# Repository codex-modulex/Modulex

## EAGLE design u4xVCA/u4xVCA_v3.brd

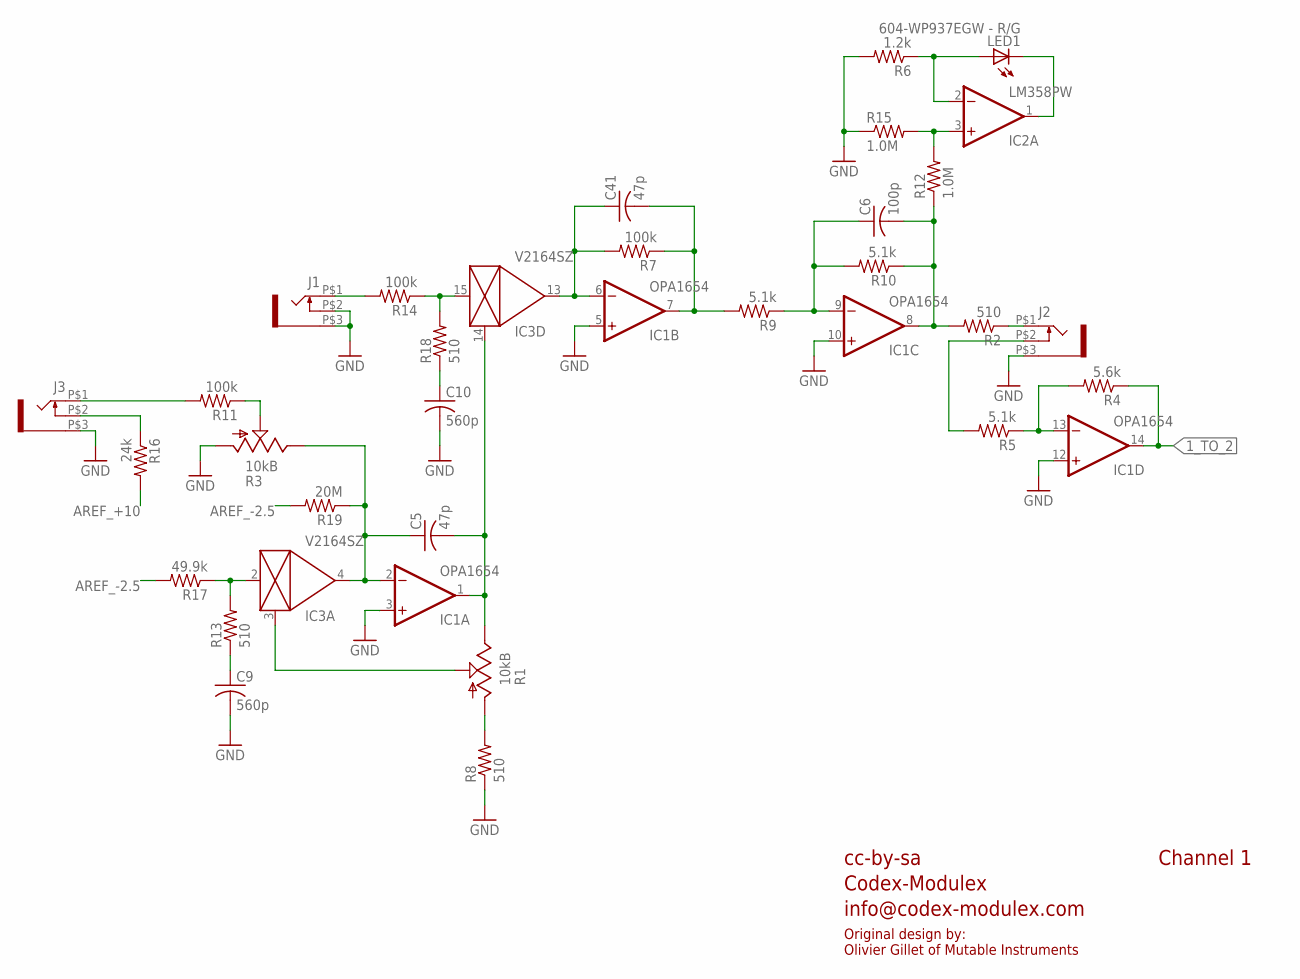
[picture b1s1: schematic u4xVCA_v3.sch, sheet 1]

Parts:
C5, C41: 47p; C0603
C6: 100p; C0603
C9, C10: 560p; C0603
IC1: OPA1654; TSSOP14
IC2: LM358PW; TSSOP8
IC3: V2164SZ; SOIC16N
J1, J2, J3: WQP-PJ301M-12_JACK
LED1: 604-WP937EGW - R/G; LED3MM
R1, R3: 10kB; ALPS_POT_VERTICAL
R2, R13, R18: 510; PARTS_AMAN_RESISTOR_0603
R4: 5.6k; PARTS_AMAN_RESISTOR_0603
R5, R9, R10: 5.1k; PARTS_AMAN_RESISTOR_0603
R6: 1.2k; PARTS_AMAN_RESISTOR_0603
R7, R11, R14: 100k; PARTS_AMAN_RESISTOR_0603
R8: 510; R0603
R12, R15: 1.0M; PARTS_AMAN_RESISTOR_0603
R16: 24k; PARTS_AMAN_RESISTOR_0603
R17: 49.9k; PARTS_AMAN_RESISTOR_0603
R19: 20M; PARTS_AMAN_RESISTOR_0603

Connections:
1_TO_2: IC1.14 (OUT), R4.1; also elsewhere on the board
AREF_+10: R16.2; also elsewhere on the board
AREF_-2.5: R17.2, R19.2; also elsewhere on the board
CV_IN_1: J3.P$1 (2), R11.2
FOO: IC3.2 (IN), R13.2, R17.1
GND: C9.2, C10.2, IC1.3 (+IN), IC1.5 (+IN), IC1.10 (+IN), IC1.12 (+IN), J1.P$2 (3), J1.P$3 (1), J2.P$3 (1), J3.P$3 (1), R3.P$3 (A), R6.2, R8.1, R15.1; also elsewhere on the board
unnamed: IC2.3 (+IN), R12.2, R15.2
unnamed: J2.P$1 (2), R2.1
unnamed: IC3.3 (CTRL), R1.P$2 (S)
unnamed: C6.1, IC1.9 (-IN), R9.1, R10.2
unnamed: R3.P$2 (S), R11.1
unnamed: R1.P$3 (A), R8.2
unnamed: IC2.1 (OUT), LED1.K (C)
unnamed: IC2.2 (-IN), LED1.A, R6.1
unnamed: C9.1, R13.1
unnamed: J3.P$2 (3), R16.1
unnamed: IC1.13 (-IN), R4.2, R5.1
unnamed: J2.P$2 (3), R5.2
unnamed: C10.1, R18.1
unnamed: C5.1, IC1.2 (-IN), IC3.4 (OUT), R3.P$1 (E), R19.1
unnamed: J1.P$1 (2), R14.2
unnamed: IC3.15 (IN), R14.1, R18.2
unnamed: C5.2, IC1.1 (OUT), IC3.14 (CTRL), R1.P$1 (E)
unnamed: C41.1, IC1.6 (-IN), IC3.13 (OUT), R7.2
unnamed: C41.2, IC1.7 (OUT), R7.1, R9.2
OUT1: C6.2, IC1.8 (OUT), R2.2, R10.1, R12.1

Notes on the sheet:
cc-by-sa
Codex-Modulex
info@codex-modulex.com
Channel 1
Original design by: Olivier Gillet of Mutable Instruments

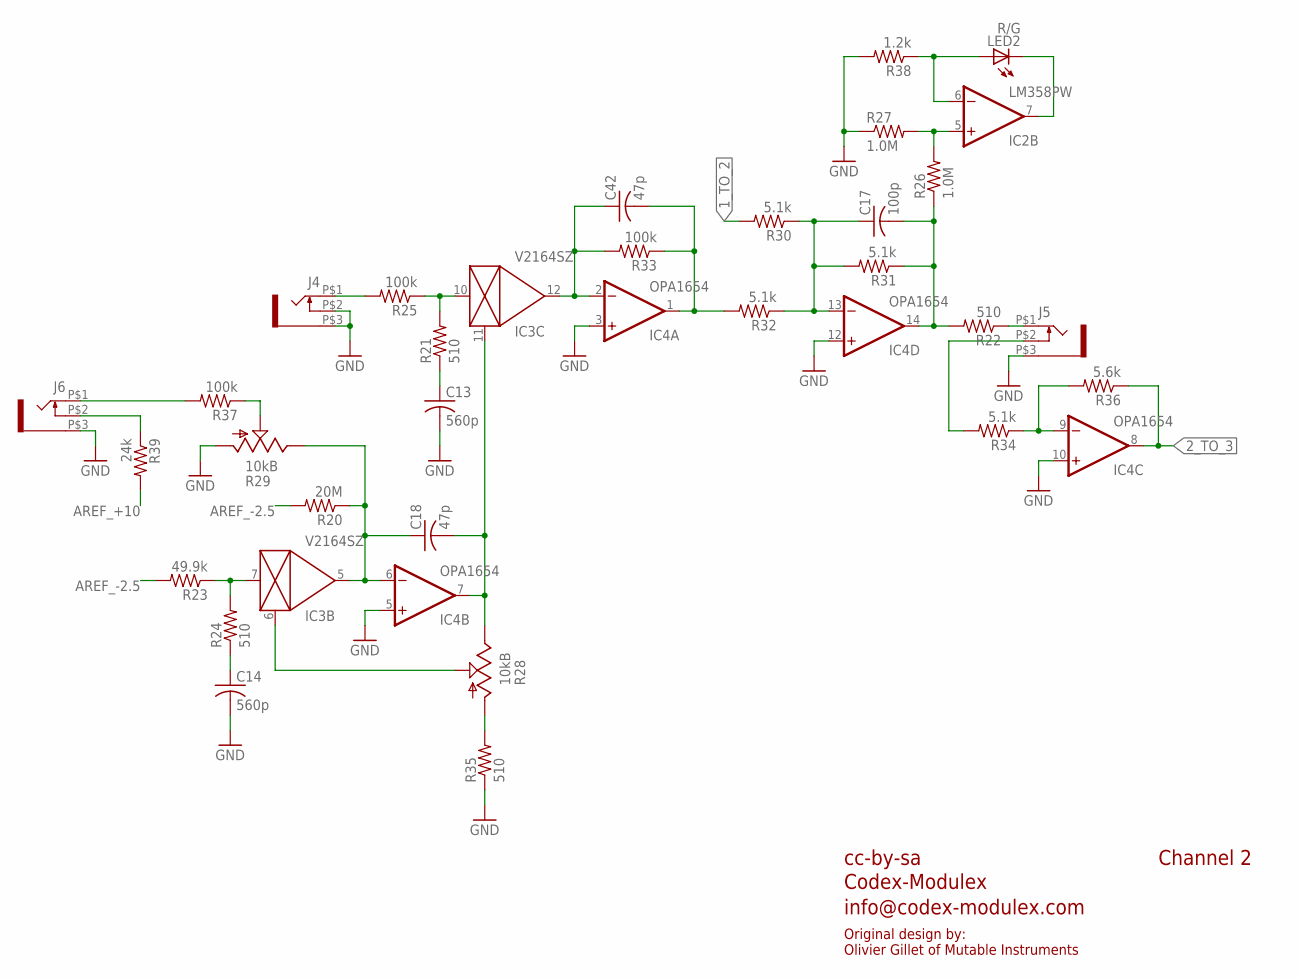
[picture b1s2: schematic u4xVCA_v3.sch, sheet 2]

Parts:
C13, C14: 560p; C0603
C17: 100p; C0603
C18, C42: 47p; C0603
IC2: LM358PW; TSSOP8
IC3: V2164SZ; SOIC16N
IC4: OPA1654; TSSOP14
J4, J5, J6: WQP-PJ301M-12_JACK
LED2: R/G; LED3MM
R20: 20M; PARTS_AMAN_RESISTOR_0603
R21, R24: 510; PARTS_AMAN_RESISTOR_0603
R22, R35: 510; R0603
R23: 49.9k; PARTS_AMAN_RESISTOR_0603
R25, R33, R37: 100k; PARTS_AMAN_RESISTOR_0603
R26, R27: 1.0M; PARTS_AMAN_RESISTOR_0603
R28, R29: 10kB; ALPS_POT_VERTICAL
R30, R31, R32, R34: 5.1k; PARTS_AMAN_RESISTOR_0603
R36: 5.6k; PARTS_AMAN_RESISTOR_0603
R38: 1.2k; PARTS_AMAN_RESISTOR_0603
R39: 24k; PARTS_AMAN_RESISTOR_0603

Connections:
1_TO_2: R30.2; also elsewhere on the board
2_TO_3: IC4.8 (OUT), R36.1; also elsewhere on the board
AREF_+10: R39.2; also elsewhere on the board
AREF_-2.5: R20.2, R23.2; also elsewhere on the board
FOO1: IC3.7 (IN), R23.1, R24.2
GND: C13.2, C14.2, IC4.3 (+IN), IC4.5 (+IN), IC4.10 (+IN), IC4.12 (+IN), J4.P$2 (3), J4.P$3 (1), J5.P$3 (1), J6.P$3 (1), R27.1, R29.P$3 (A), R35.1, R38.2; also elsewhere on the board
unnamed: J4.P$1 (2), R25.2
unnamed: IC2.5 (+IN), R26.2, R27.2
unnamed: J5.P$1 (2), R22.1
unnamed: C13.1, R21.1
unnamed: IC3.10 (IN), R21.2, R25.1
unnamed: IC3.6 (CTRL), R28.P$2 (S)
unnamed: C17.1, IC4.13 (-IN), R30.1, R31.2, R32.1
unnamed: C18.2, IC3.11 (CTRL), IC4.7 (OUT), R28.P$1 (E)
unnamed: R28.P$3 (A), R35.2
unnamed: IC2.7 (OUT), LED2.K (C)
unnamed: IC2.6 (-IN), LED2.A, R38.1
unnamed: IC4.9 (-IN), R34.1, R36.2
unnamed: J5.P$2 (3), R34.2
unnamed: C42.2, IC4.1 (OUT), R32.2, R33.1
unnamed: R29.P$2 (S), R37.1
unnamed: C14.1, R24.1
unnamed: C18.1, IC3.5 (OUT), IC4.6 (-IN), R20.1, R29.P$1 (E)
unnamed: J6.P$1 (2), R37.2
unnamed: C42.1, IC3.12 (OUT), IC4.2 (-IN), R33.2
unnamed: J6.P$2 (3), R39.1
OUT2: C17.2, IC4.14 (OUT), R22.2, R26.1, R31.1

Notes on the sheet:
cc-by-sa
Codex-Modulex
info@codex-modulex.com
Channel 2
Original design by: Olivier Gillet of Mutable Instruments

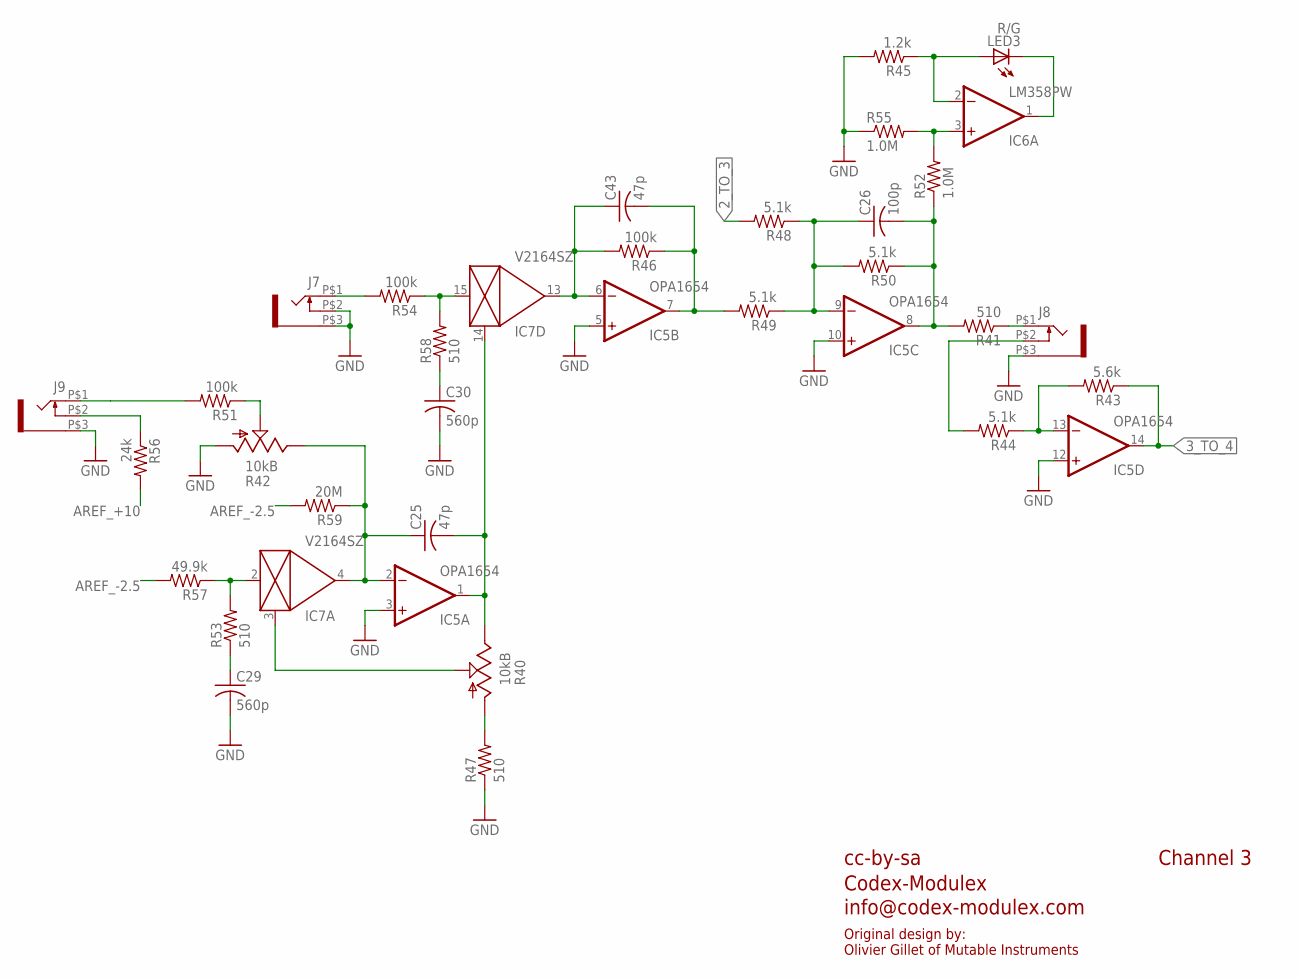
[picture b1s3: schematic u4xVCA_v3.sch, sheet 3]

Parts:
C25, C43: 47p; C0603
C26: 100p; C0603
C29, C30: 560p; C0603
IC5: OPA1654; TSSOP14
IC6: LM358PW; TSSOP8
IC7: V2164SZ; SOIC16N
J7, J8, J9: WQP-PJ301M-12_JACK
LED3: R/G; LED3MM
R40, R42: 10kB; ALPS_POT_VERTICAL
R41, R47, R53, R58: 510; PARTS_AMAN_RESISTOR_0603
R43: 5.6k; PARTS_AMAN_RESISTOR_0603
R44, R48, R49, R50: 5.1k; PARTS_AMAN_RESISTOR_0603
R45: 1.2k; PARTS_AMAN_RESISTOR_0603
R46, R51, R54: 100k; PARTS_AMAN_RESISTOR_0603
R52, R55: 1.0M; PARTS_AMAN_RESISTOR_0603
R56: 24k; PARTS_AMAN_RESISTOR_0603
R57: 49.9k; PARTS_AMAN_RESISTOR_0603
R59: 20M; PARTS_AMAN_RESISTOR_0603

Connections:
2_TO_3: R48.2; also elsewhere on the board
3_TO_4: IC5.14 (OUT), R43.1; also elsewhere on the board
AREF_+10: R56.2; also elsewhere on the board
AREF_-2.5: R57.2, R59.2; also elsewhere on the board
FOO2: IC7.2 (IN), R53.2, R57.1
GND: C29.2, C30.2, IC5.3 (+IN), IC5.5 (+IN), IC5.10 (+IN), IC5.12 (+IN), J7.P$2 (3), J7.P$3 (1), J8.P$3 (1), J9.P$3 (1), R42.P$3 (A), R45.2, R47.1, R55.1; also elsewhere on the board
unnamed: IC6.3 (+IN), R52.2, R55.2
unnamed: J8.P$1 (2), R41.1
unnamed: IC7.3 (CTRL), R40.P$2 (S)
unnamed: C25.2, IC5.1 (OUT), IC7.14 (CTRL), R40.P$1 (E)
unnamed: R40.P$3 (A), R47.2
unnamed: C30.1, R58.1
unnamed: IC7.15 (IN), R54.1, R58.2
unnamed: C26.1, IC5.9 (-IN), R48.1, R49.1, R50.2
unnamed: J9.P$2 (3), R56.1
unnamed: J7.P$1 (2), R54.2
unnamed: J9.P$1 (2), R51.2
unnamed: C43.1, IC5.6 (-IN), IC7.13 (OUT), R46.2
unnamed: IC6.1 (OUT), LED3.K (C)
unnamed: IC6.2 (-IN), LED3.A, R45.1
unnamed: IC5.13 (-IN), R43.2, R44.1
unnamed: J8.P$2 (3), R44.2
unnamed: C29.1, R53.1
unnamed: C25.1, IC5.2 (-IN), IC7.4 (OUT), R42.P$1 (E), R59.1
unnamed: R42.P$2 (S), R51.1
unnamed: C43.2, IC5.7 (OUT), R46.1, R49.2
OUT3: C26.2, IC5.8 (OUT), R41.2, R50.1, R52.1

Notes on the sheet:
cc-by-sa
Codex-Modulex
info@codex-modulex.com
Channel 3
Original design by: Olivier Gillet of Mutable Instruments

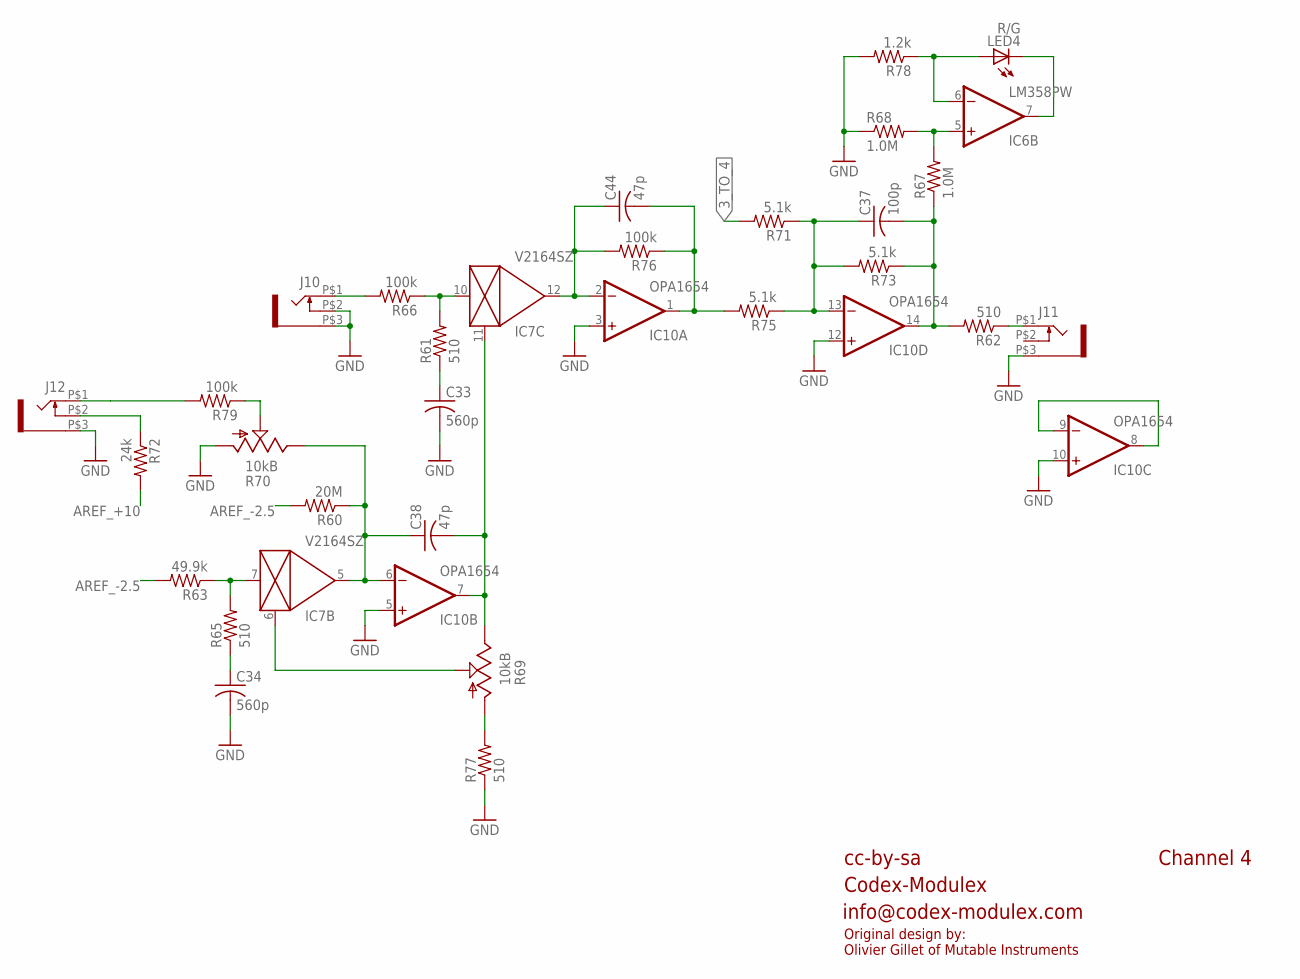
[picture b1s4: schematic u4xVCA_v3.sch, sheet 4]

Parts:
C33, C34: 560p; C0603
C37: 100p; C0603
C38, C44: 47p; C0603
IC6: LM358PW; TSSOP8
IC7: V2164SZ; SOIC16N
IC10: OPA1654; TSSOP14
J10, J11, J12: WQP-PJ301M-12_JACK
LED4: R/G; LED3MM
R60: 20M; PARTS_AMAN_RESISTOR_0603
R61, R62, R65, R77: 510; PARTS_AMAN_RESISTOR_0603
R63: 49.9k; PARTS_AMAN_RESISTOR_0603
R66, R76, R79: 100k; PARTS_AMAN_RESISTOR_0603
R67, R68: 1.0M; PARTS_AMAN_RESISTOR_0603
R69, R70: 10kB; ALPS_POT_VERTICAL
R71, R73, R75: 5.1k; PARTS_AMAN_RESISTOR_0603
R72: 24k; PARTS_AMAN_RESISTOR_0603
R78: 1.2k; PARTS_AMAN_RESISTOR_0603

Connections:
3_TO_4: R71.2; also elsewhere on the board
AREF_+10: R72.2; also elsewhere on the board
AREF_-2.5: R60.2, R63.2; also elsewhere on the board
FOO3: IC7.7 (IN), R63.1, R65.2
GND: C33.2, C34.2, IC10.3 (+IN), IC10.5 (+IN), IC10.10 (+IN), IC10.12 (+IN), J10.P$2 (3), J10.P$3 (1), J11.P$3 (1), J12.P$3 (1), R68.1, R70.P$3 (A), R77.1, R78.2; also elsewhere on the board
unnamed: IC10.8 (OUT), IC10.9 (-IN)
unnamed: IC6.5 (+IN), R67.2, R68.2
unnamed: C38.2, IC7.11 (CTRL), IC10.7 (OUT), R69.P$1 (E)
unnamed: IC7.6 (CTRL), R69.P$2 (S)
unnamed: R69.P$3 (A), R77.2
unnamed: C44.1, IC7.12 (OUT), IC10.2 (-IN), R76.2
unnamed: J10.P$1 (2), R66.2
unnamed: J11.P$1 (2), R62.1
unnamed: C33.1, R61.1
unnamed: IC7.10 (IN), R61.2, R66.1
unnamed: C37.1, IC10.13 (-IN), R71.1, R73.2, R75.1
unnamed: J12.P$1 (2), R79.2
unnamed: IC6.7 (OUT), LED4.K (C)
unnamed: IC6.6 (-IN), LED4.A, R78.1
unnamed: C44.2, IC10.1 (OUT), R75.2, R76.1
unnamed: R70.P$2 (S), R79.1
unnamed: C34.1, R65.1
unnamed: C38.1, IC7.5 (OUT), IC10.6 (-IN), R60.1, R70.P$1 (E)
unnamed: J12.P$2 (3), R72.1
OUT4: C37.2, IC10.14 (OUT), R62.2, R67.1, R73.1

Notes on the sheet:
cc-by-sa
Codex-Modulex
info@codex-modulex.com
Channel 4
Original design by: Olivier Gillet of Mutable Instruments

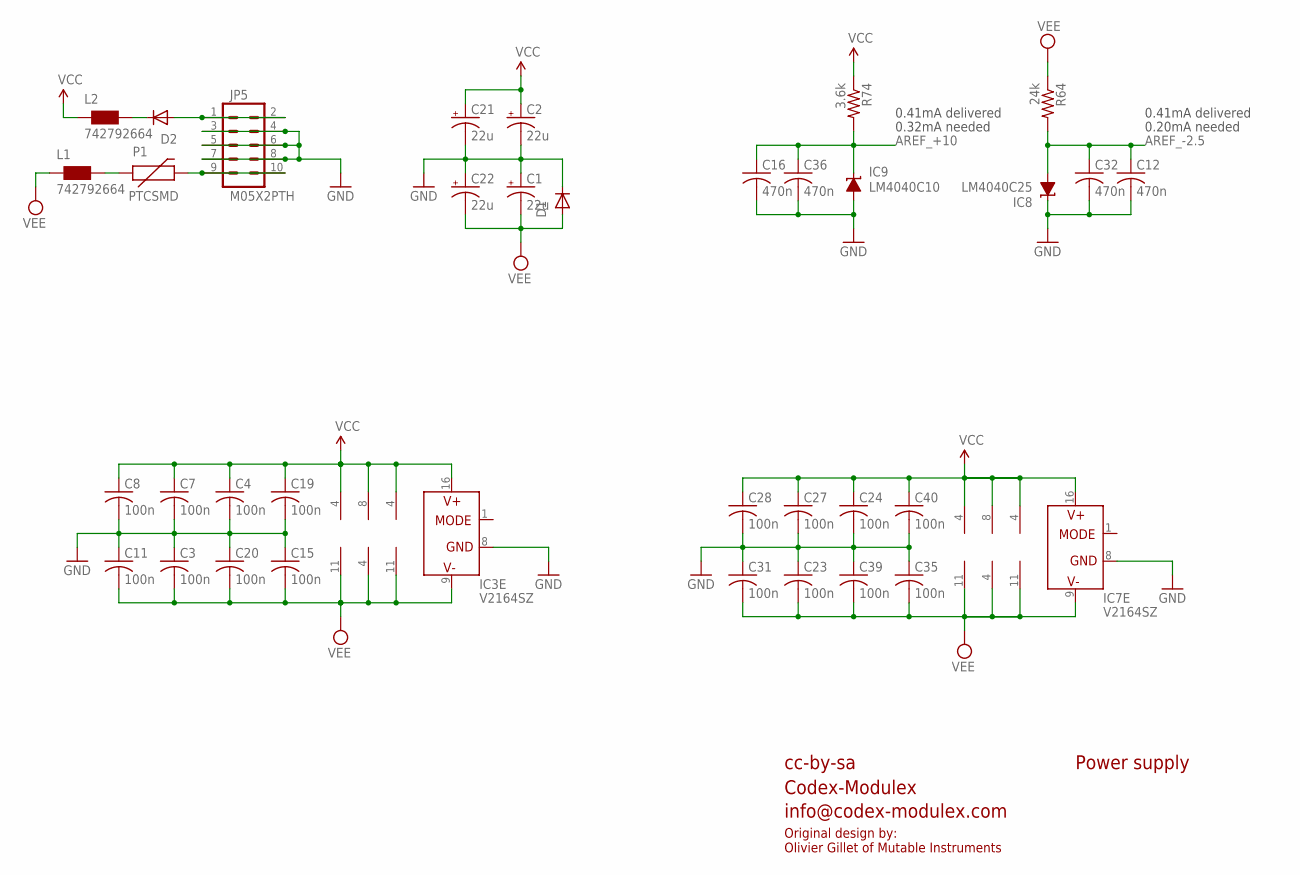
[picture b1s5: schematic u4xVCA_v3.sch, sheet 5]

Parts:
C1, C2, C21, C22: 22u; PANASONIC_B
C3, C4, C7, C8, C11, C15, C19, C20, C23, C24, C27, C28, C31, C35, C39, C40: 100n; C0603
C12, C16, C32, C36: 470n; C0603
D1, D2: 1N5819HW; SOD123
IC1, IC4, IC5, IC10: OPA1654; TSSOP14
IC2, IC6: LM358PW; TSSOP8
IC3, IC7: V2164SZ; SOIC16N
IC8: LM4040C25; DBZ_R-PDSO-G3
IC9: LM4040C10; DBZ_R-PDSO-G3
JP5: M05X2PTH; AVR_ICSP
L1, L2: 742792664; 0603
P1: PTCSMD; PTC-1206
R64: 24k; PARTS_AMAN_RESISTOR_0603
R74: 3.6k; PARTS_AMAN_RESISTOR_0603

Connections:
AREF_+10: C16.1, C36.1, IC9.1 (C), R74.2; also elsewhere on the board
AREF_-2.5: C12.1, C32.1, IC8.2 (A), R64.2; also elsewhere on the board
GND: C1.+, C2.-, C3.1, C4.2, C7.2, C8.2, C11.1, C12.2, C15.1, C16.2, C19.2, C20.1, C21.-, C22.+, C23.1, C24.2, C27.2, C28.2, C31.1, C32.2, C35.1, C36.2, C39.1, C40.2, D1.C, IC3.8 (GND), IC7.8 (GND), IC8.1 (C), IC9.2 (A), JP5.3, JP5.4, JP5.5, JP5.6, JP5.7, JP5.8; also elsewhere on the board
unnamed: D2.A, JP5.1, JP5.2
unnamed: JP5.9, JP5.10, P1.2
unnamed: L1.2, P1.1
unnamed: D2.C, L2.2
VCC: C2.+, C4.1, C7.1, C8.1, C19.1, C21.+, C24.1, C27.1, C28.1, C40.1, IC1.4 (V+), IC2.8 (V+), IC3.16 (V+), IC4.4 (V+), IC5.4 (V+), IC6.8 (V+), IC7.16 (V+), IC10.4 (V+), L2.1, R74.1
VEE: C1.-, C3.2, C11.2, C15.2, C20.2, C22.-, C23.2, C31.2, C35.2, C39.2, D1.A, IC1.11 (V-), IC2.4 (V-), IC3.9 (V-), IC4.11 (V-), IC5.11 (V-), IC6.4 (V-), IC7.9 (V-), IC10.11 (V-), L1.1, R64.1

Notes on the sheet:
cc-by-sa
Codex-Modulex
info@codex-modulex.com
Power supply
0.41mA delivered
0.20mA needed
0.32mA needed
Original design by: Olivier Gillet of Mutable Instruments

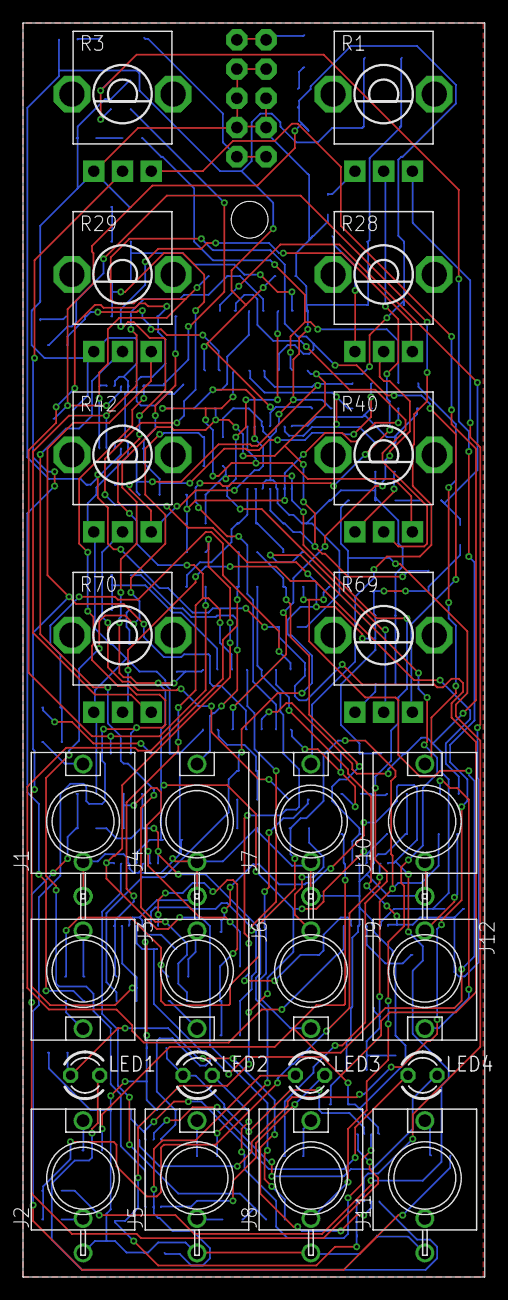
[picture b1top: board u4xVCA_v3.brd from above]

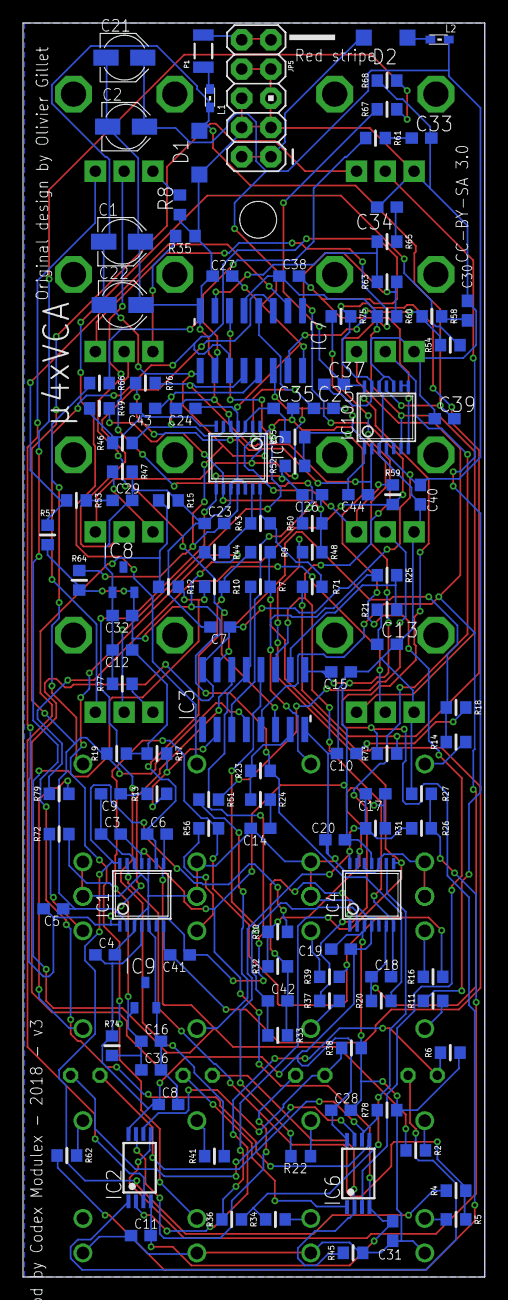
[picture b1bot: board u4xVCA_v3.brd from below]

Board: 2 copper layers, 40.1 x 109.0 mm, 155 parts (131 on the bottom side), 99 nets.

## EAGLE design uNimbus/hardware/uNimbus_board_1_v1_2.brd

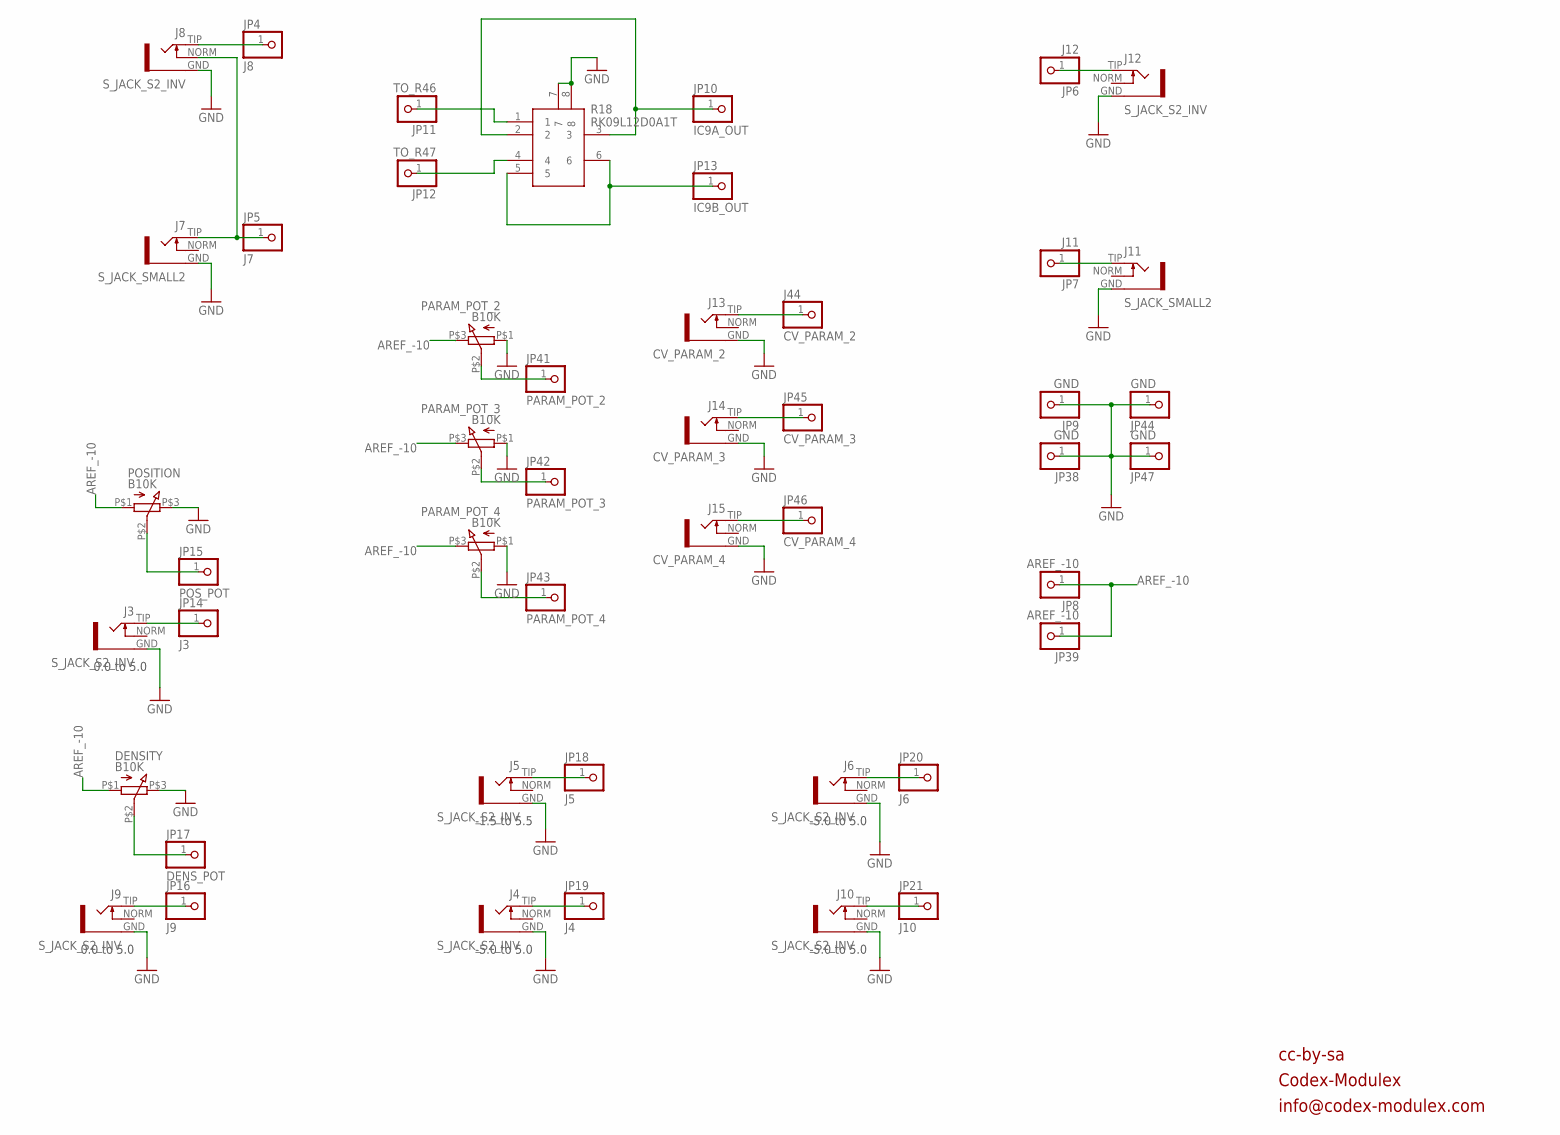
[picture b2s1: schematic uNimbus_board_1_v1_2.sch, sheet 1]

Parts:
DENSITY: B10K; Q-POT2
J3, J4, J5, J6, J8, J9, J10, J12: S_JACK_S2_INV
J7, J11: S_JACK_SMALL2
J13: CV_PARAM_2; S_JACK_S2_INV
J14: CV_PARAM_3; S_JACK_S2_INV
J15: CV_PARAM_4; S_JACK_S2_INV
J44: CV_PARAM_2; PARTS_AMAN_1X01
JP4: J8; PARTS_AMAN_1X01
JP5: J7; PARTS_AMAN_1X01
JP6: J12; PARTS_AMAN_1X01
JP7: J11; PARTS_AMAN_1X01
JP8, JP39: AREF_-10; PARTS_AMAN_1X01
JP9, JP38, JP44, JP47: GND; PARTS_AMAN_1X01
JP10: IC9A_OUT; PARTS_AMAN_1X01
JP11: TO_R46; PARTS_AMAN_1X01
JP12: TO_R47; PARTS_AMAN_1X01
JP13: IC9B_OUT; PARTS_AMAN_1X01
JP14: J3; PARTS_AMAN_1X01
JP15: POS_POT; PARTS_AMAN_1X01
JP16: J9; PARTS_AMAN_1X01
JP17: DENS_POT; PARTS_AMAN_1X01
JP18: J5; PARTS_AMAN_1X01
JP19: J4; PARTS_AMAN_1X01
JP20: J6; PARTS_AMAN_1X01
JP21: J10; PARTS_AMAN_1X01
JP41: PARAM_POT_2; PARTS_AMAN_1X01
JP42: PARAM_POT_3; PARTS_AMAN_1X01
JP43: PARAM_POT_4; PARTS_AMAN_1X01
JP45: CV_PARAM_3; PARTS_AMAN_1X01
JP46: CV_PARAM_4; PARTS_AMAN_1X01
PARAM_POT_2, PARAM_POT_3, PARAM_POT_4: B10K; Q-POT2
POSITION: B10K; Q-POT2
R18: RK09L12D0A1T

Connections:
AREF_-10: DENSITY.P$1 (1), JP8.1, JP39.1, PARAM_POT_2.P$3 (3), PARAM_POT_3.P$3 (3), PARAM_POT_4.P$3 (3), POSITION.P$1 (1)
GND: DENSITY.P$3 (3), J3.GND, J4.GND, J5.GND, J6.GND, J7.GND, J8.GND, J9.GND, J10.GND, J11.GND, J12.GND, J13.GND, J14.GND, J15.GND, JP9.1, JP38.1, JP44.1, JP47.1, PARAM_POT_2.P$1 (1), PARAM_POT_3.P$1 (1), PARAM_POT_4.P$1 (1), POSITION.P$3 (3), R18.7, R18.8; also elsewhere on the board
LOUT_JACK: J11.TIP, JP7.1
unnamed: J4.TIP, JP19.1
unnamed: J10.TIP, JP21.1
unnamed: J6.TIP, JP20.1
unnamed: J5.TIP, JP18.1
unnamed: J9.TIP, JP16.1
unnamed: JP12.1, R18.4
unnamed: J8.TIP, JP4.1
unnamed: J7.TIP, J8.NORM, JP5.1
unnamed: JP13.1, R18.5, R18.6
unnamed: JP42.1, PARAM_POT_3.P$2 (2)
unnamed: DENSITY.P$2 (2), JP17.1
unnamed: J3.TIP, JP14.1
unnamed: JP43.1, PARAM_POT_4.P$2 (2)
unnamed: JP41.1, PARAM_POT_2.P$2 (2)
unnamed: JP11.1, R18.1
unnamed: J15.TIP, JP46.1
unnamed: J14.TIP, JP45.1
unnamed: JP15.1, POSITION.P$2 (2)
unnamed: J13.TIP, J44.1
unnamed: JP10.1, R18.2, R18.3
ROUT_JACK: J12.TIP, JP6.1

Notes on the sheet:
cc-by-sa
Codex-Modulex
info@codex-modulex.com
0.0 to 5.0
-1.5 to 5.5
-5.0 to 5.0

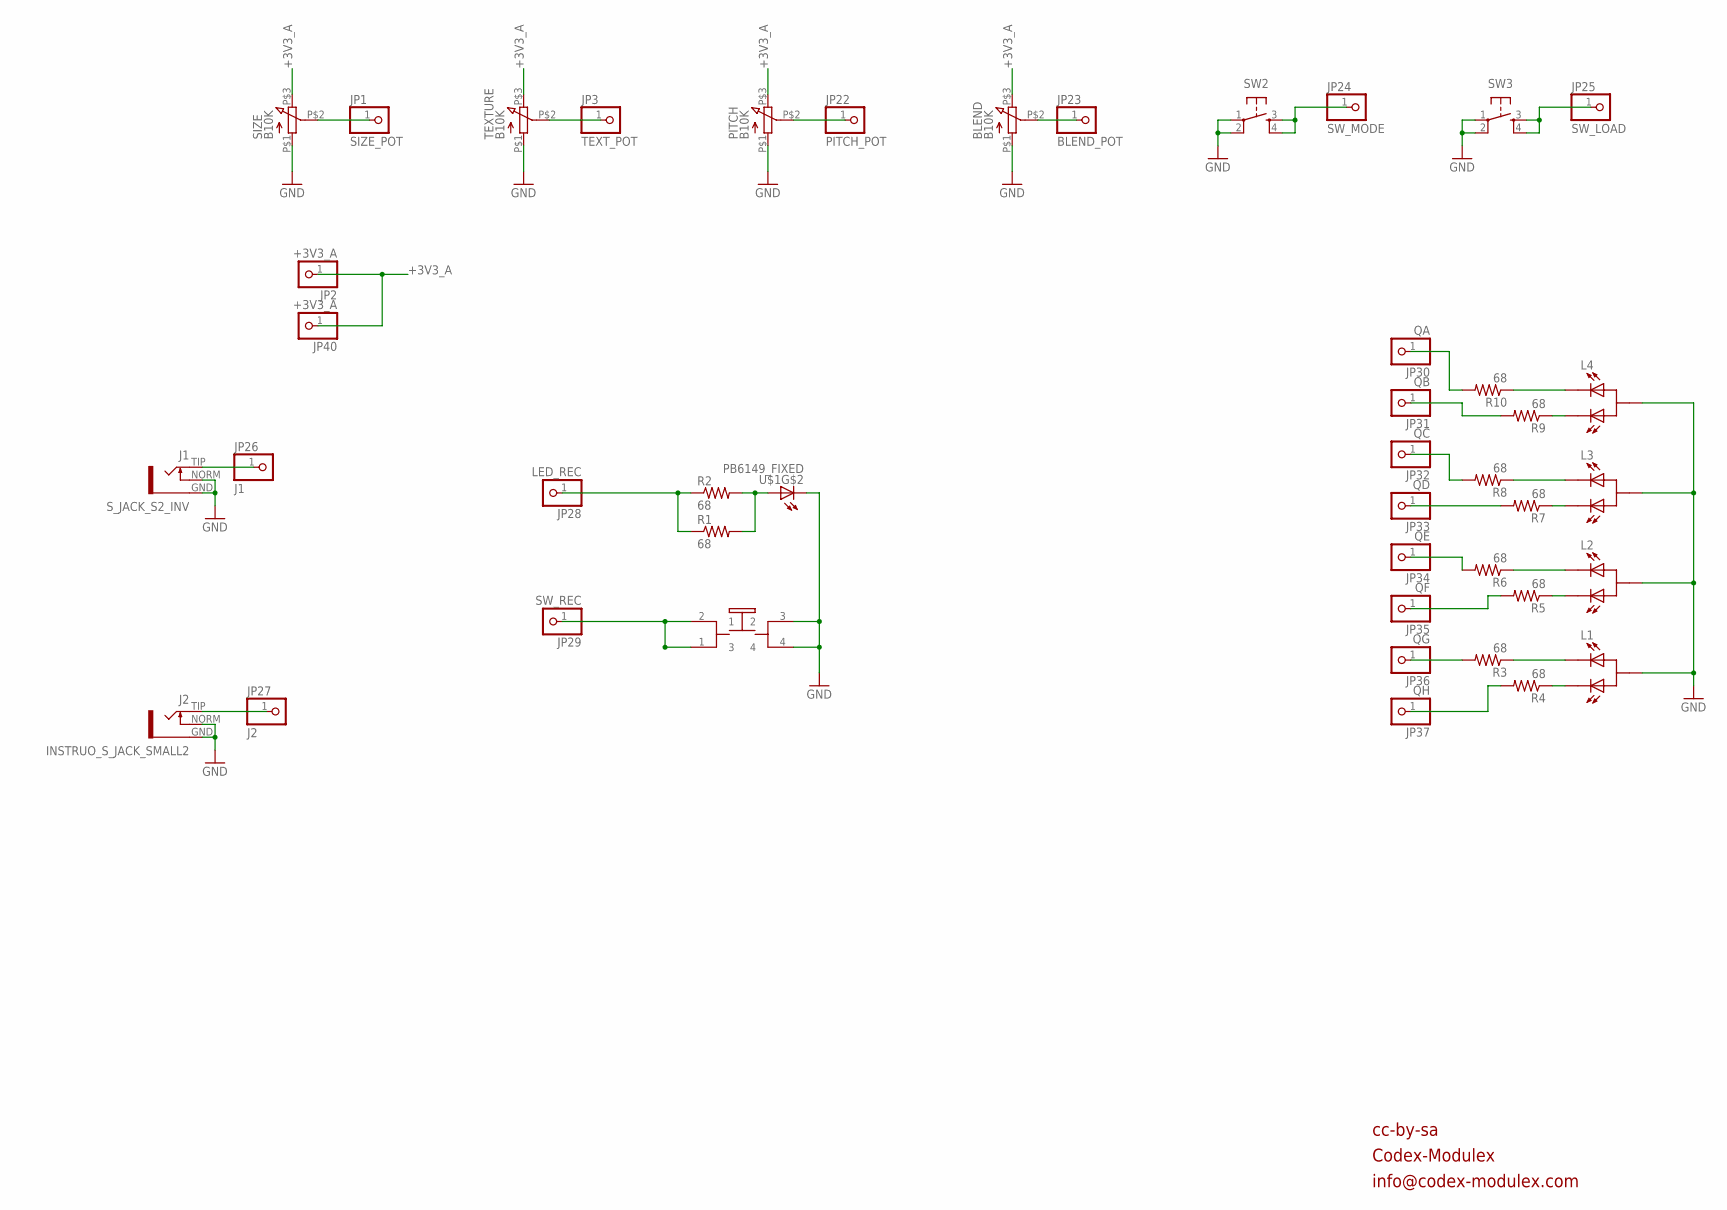
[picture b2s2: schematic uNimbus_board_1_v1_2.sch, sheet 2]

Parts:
BLEND: B10K; Q-POT2
J1: S_JACK_S2_INV
J2: INSTRUO_S_JACK_SMALL2
JP1: SIZE_POT; PARTS_AMAN_1X01
JP2, JP40: +3V3_A; PARTS_AMAN_1X01
JP3: TEXT_POT; PARTS_AMAN_1X01
JP22: PITCH_POT; PARTS_AMAN_1X01
JP23: BLEND_POT; PARTS_AMAN_1X01
JP24: SW_MODE; PARTS_AMAN_1X01
JP25: SW_LOAD; PARTS_AMAN_1X01
JP26: J1; PARTS_AMAN_1X01
JP27: J2; PARTS_AMAN_1X01
JP28: LED_REC; PARTS_AMAN_1X01
JP29: SW_REC; PARTS_AMAN_1X01
JP30: QA; PARTS_AMAN_1X01
JP31: QB; PARTS_AMAN_1X01
JP32: QC; PARTS_AMAN_1X01
JP33: QD; PARTS_AMAN_1X01
JP34: QE; PARTS_AMAN_1X01
JP35: QF; PARTS_AMAN_1X01
JP36: QG; PARTS_AMAN_1X01
JP37: QH; PARTS_AMAN_1X01
L1, L2, L3, L4: LED_3MM_3PIN
PITCH: B10K; Q-POT2
R1, R2, R3, R4, R5, R6, R7, R8, R9, R10: 68; R0603
SIZE: B10K; Q-POT2
SW2, SW3: TAC_SWITCHPTH; TACTILE-PTH
TEXTURE: B10K; Q-POT2
U$1: PB6149_FIXED; PB6149L

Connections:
+3V3_A: BLEND.P$3 (3), JP2.1, JP40.1, PITCH.P$3 (3), SIZE.P$3 (3), TEXTURE.P$3 (3)
GND: BLEND.P$1 (1), J1.GND, J1.NORM, J2.GND, J2.NORM, L1.A, L2.A, L3.A, L4.A, PITCH.P$1 (1), SIZE.P$1 (1), SW2.1, SW2.2, SW3.1, SW3.2, TEXTURE.P$1 (1), U$1.3 (2), U$1.4, U$1.K (C); also elsewhere on the board
LED_REC: JP28.1, R1.1, R2.1
unnamed: JP1.1, SIZE.P$2 (2)
unnamed: JP3.1, TEXTURE.P$2 (2)
unnamed: JP22.1, PITCH.P$2 (2)
unnamed: BLEND.P$2 (2), JP23.1
unnamed: JP30.1, R10.2
unnamed: L4.C1, R9.1
unnamed: JP31.1, R9.2
unnamed: L4.C2, R10.1
unnamed: JP33.1, R7.2
unnamed: JP34.1, R6.2
unnamed: L3.C2, R8.1
unnamed: JP35.1, R5.2
unnamed: JP36.1, R3.2
unnamed: JP37.1, R4.2
unnamed: JP32.1, R8.2
unnamed: L3.C1, R7.1
unnamed: L2.C2, R6.1
unnamed: J2.TIP, JP27.1
unnamed: R1.2, R2.2, U$1.A
unnamed: L2.C1, R5.1
unnamed: L1.C2, R3.1
unnamed: L1.C1, R4.1
unnamed: J1.TIP, JP26.1
SW_LOAD: JP25.1, SW3.3, SW3.4
SW_MODE: JP24.1, SW2.3, SW2.4
SW_REC: JP29.1, U$1.1 (3), U$1.2 (1)

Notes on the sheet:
cc-by-sa
Codex-Modulex
info@codex-modulex.com

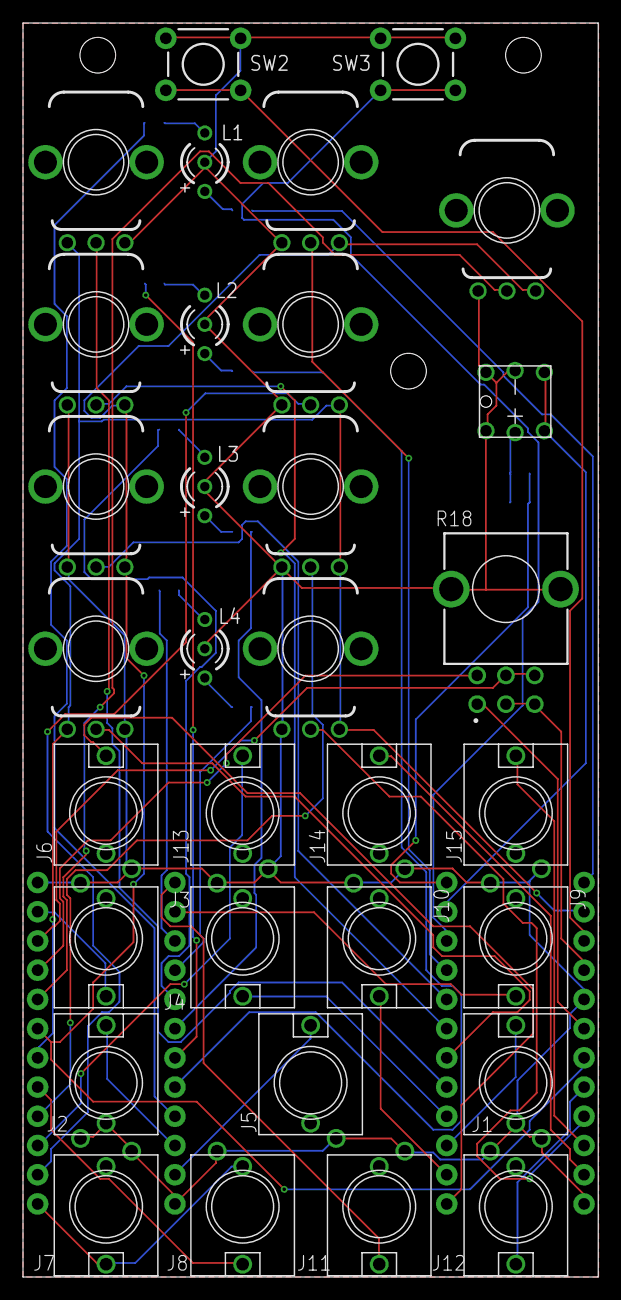
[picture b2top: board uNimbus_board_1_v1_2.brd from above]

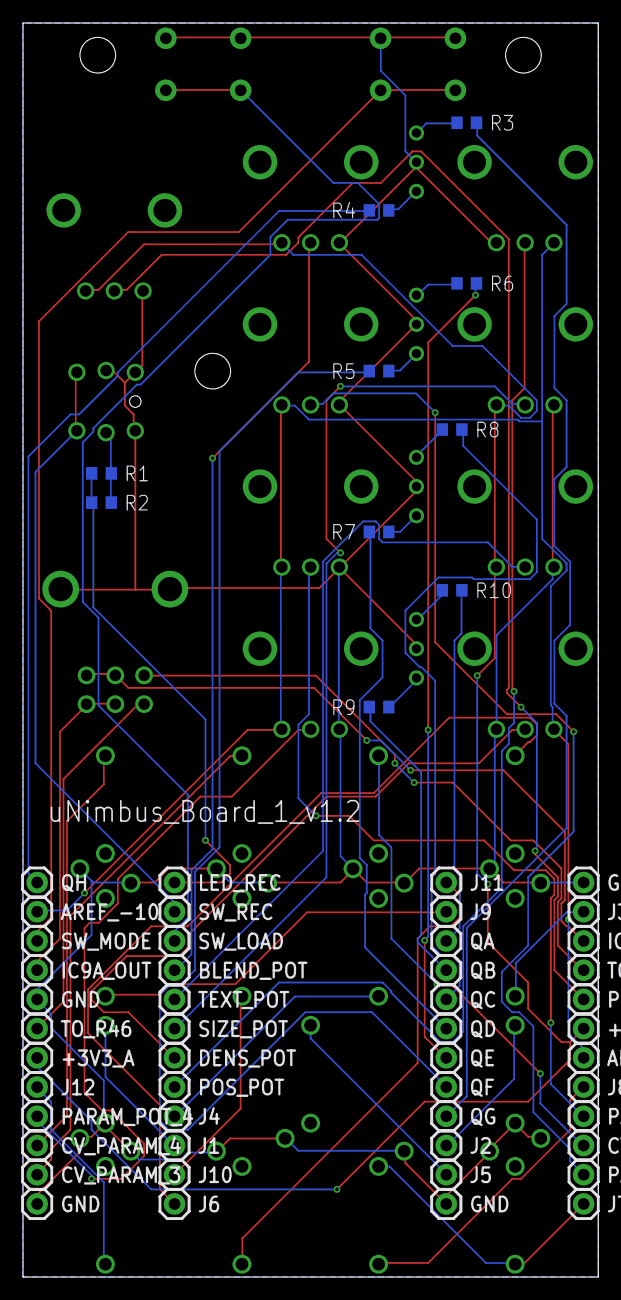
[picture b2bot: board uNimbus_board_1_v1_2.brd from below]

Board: 2 copper layers, 50.0 x 109.0 mm, 90 parts (58 on the bottom side), 52 nets.

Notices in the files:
u4xVCA/u4xVCA_v3.brd:
CC-BY-SA 3.0
parts and their libraries:
SparkFun-DigitalIC: Licensing: CC v3.0 Share-Alike You are welcome to use this library for commercial purposes.
